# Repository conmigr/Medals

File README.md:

# Medals
PCB Medal Designs

Round shaped PCB designs using Eagle software that can be used as badges or awards.  These are a series of medals that can be used to help people learn the basics of making a PCB badge or iot device.

Nobel Prize Award - This PCB schematic and board usually is awarded to individuals for writing articles, blogs, or other material that contributess to the profession of information and cyber security.

Automator Award - This PCB schematic and board usually is awarded to individuals for outstanding work in the field of automation of an infosec practice.

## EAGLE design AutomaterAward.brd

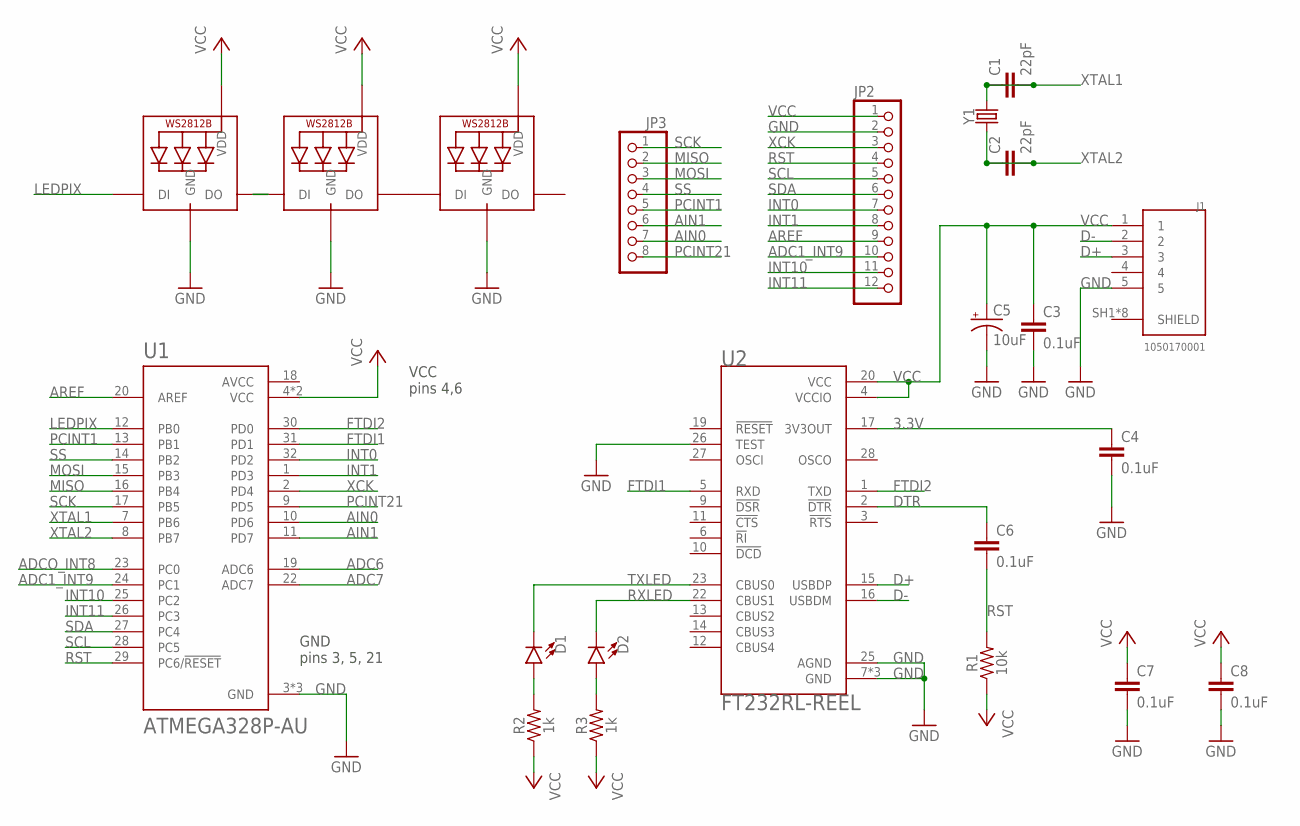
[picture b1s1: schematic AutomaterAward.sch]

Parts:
C1, C2: 22pF; 0603
C3, C4, C6, C7, C8: 0.1uF; 0603
C5: 10uF; EIA3216
D1, D2: LED0603; LED-0603
J1: 1050170001; MOLEX_1050170001
JP2: PINHD-1X12; 1X12
JP3: PINHD-1X8; 1X08
LED1, LED2, LED3: WS2812B3535; LED3535
R1: 10k; 0603
R2, R3: 1k; 0603
U1: ATMEGA328P-AU; QFP80P900X900X120-32N
U2: FT232RL-REEL; SOP65P780X200-28N
Y1: CRYSTALPTH-HC49US; HC49US

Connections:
3.3V: C4.1, U2.17 (3V3OUT)
ADC1_INT9: JP2.10, U1.24 (PC1)
ADC6: U1.19 (ADC6)
ADC7: U1.22 (ADC7)
ADCO_INT8: U1.23 (PC0)
AIN0: JP3.7, U1.10 (PD6)
AIN1: JP3.6, U1.11 (PD7)
AREF: JP2.9, U1.20 (AREF)
AVCC: U1.18 (AVCC)
D+: J1.3, U2.15 (USBDP)
D-: J1.2, U2.16 (USBDM)
DTR: C6.1, U2.2 (!DTR)
FTDI1: U1.31 (PD1), U2.5 (RXD)
FTDI2: U1.30 (PD0), U2.1 (TXD)
GND: C3.2, C4.2, C5.-, C7.2, C8.2, J1.5, JP2.2, LED1.4 (GND), LED2.4 (GND), LED3.4 (GND), U1.3 (GND), U1.5 (GND), U1.21 (GND), U2.7 (GND), U2.18 (GND), U2.21 (GND), U2.25 (AGND), U2.26 (TEST)
INT0: JP2.7, U1.32 (PD2)
INT1: JP2.8, U1.1 (PD3)
INT10: JP2.11, U1.25 (PC2)
INT11: JP2.12, U1.26 (PC3)
LEDPIX: LED1.1 (DI), U1.12 (PB0)
MISO: JP3.2, U1.16 (PB4)
MOSI: JP3.3, U1.15 (PB3)
unnamed: LED1.3 (DO), LED2.1 (DI)
unnamed: D1.A, R2.2
unnamed: D2.A, R3.2
unnamed: LED2.3 (DO), LED3.1 (DI)
PCINT1: JP3.5, U1.13 (PB1)
PCINT21: JP3.8, U1.9 (PD5)
RST: C6.2, JP2.4, R1.2, U1.29 (PC6/!RESET)
RXLED: D2.C, U2.22 (CBUS1)
SCK: JP3.1, U1.17 (PB5)
SCL: JP2.5, U1.28 (PC5)
SDA: JP2.6, U1.27 (PC4)
SS: JP3.4, U1.14 (PB2)
TXLED: D1.C, U2.23 (CBUS0)
VCC: C3.1, C5.+, C7.1, C8.1, J1.1, JP2.1, LED1.2 (VDD), LED2.2 (VDD), LED3.2 (VDD), R1.1, R2.1, R3.1, U1.4 (VCC), U1.6 (VCC), U2.4 (VCCIO), U2.20 (VCC)
XCK: JP2.3, U1.2 (PD4)
XTAL1: C1.1, C1.2, U1.7 (PB6), Y1.2
XTAL2: C2.1, C2.2, U1.8 (PB7), Y1.1

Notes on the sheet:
GND pins 3, 5, 21
VCC pins 4,6

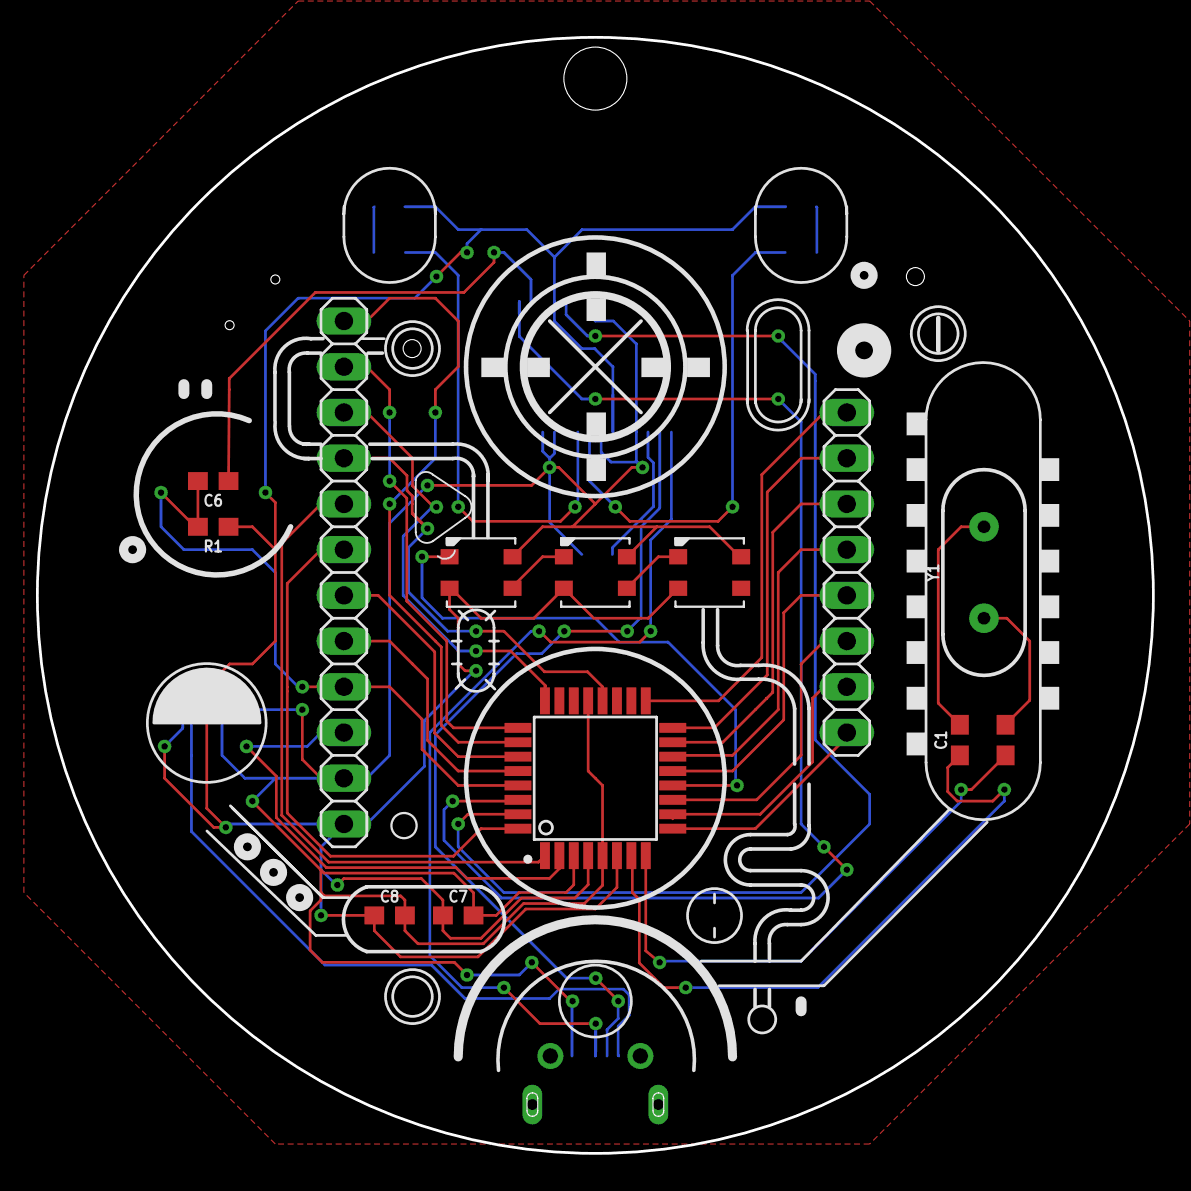
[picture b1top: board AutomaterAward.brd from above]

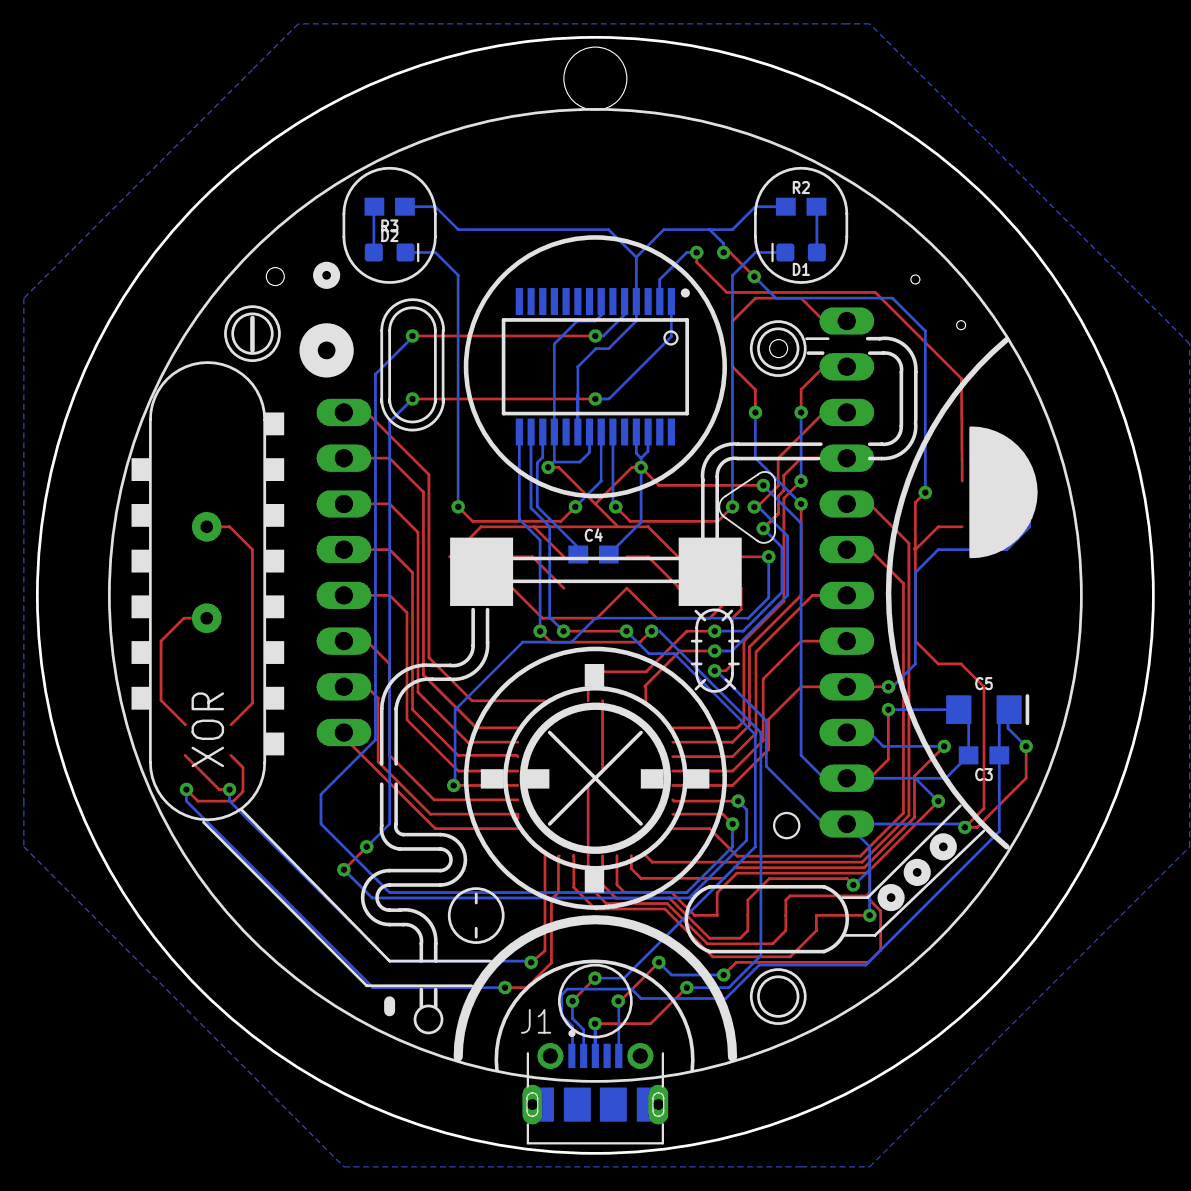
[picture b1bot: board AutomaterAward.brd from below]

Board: 2 copper layers, 62.0 x 62.0 mm, 22 parts (9 on the bottom side), 35 nets.

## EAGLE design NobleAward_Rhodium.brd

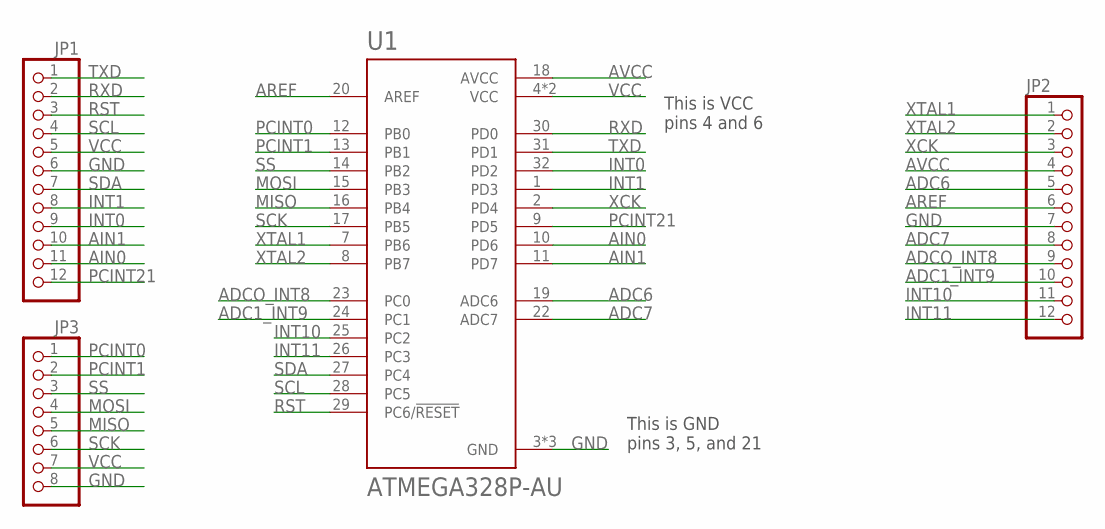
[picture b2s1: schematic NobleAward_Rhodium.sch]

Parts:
JP1, JP2: PINHD-1X12; 1X12
JP3: PINHD-1X8; 1X08
U1: ATMEGA328P-AU; QFP80P900X900X120-32N

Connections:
ADC1_INT9: JP2.10, U1.24 (PC1)
ADC6: JP2.5, U1.19 (ADC6)
ADC7: JP2.8, U1.22 (ADC7)
ADCO_INT8: JP2.9, U1.23 (PC0)
AIN0: JP1.11, U1.10 (PD6)
AIN1: JP1.10, U1.11 (PD7)
AREF: JP2.6, U1.20 (AREF)
AVCC: JP2.4, U1.18 (AVCC)
GND: JP1.6, JP2.7, JP3.8, U1.3 (GND), U1.5 (GND), U1.21 (GND)
INT0: JP1.9, U1.32 (PD2)
INT1: JP1.8, U1.1 (PD3)
INT10: JP2.11, U1.25 (PC2)
INT11: JP2.12, U1.26 (PC3)
MISO: JP3.5, U1.16 (PB4)
MOSI: JP3.4, U1.15 (PB3)
PCINT0: JP3.1, U1.12 (PB0)
PCINT1: JP3.2, U1.13 (PB1)
PCINT21: JP1.12, U1.9 (PD5)
RST: JP1.3, U1.29 (PC6/!RESET)
RXD: JP1.2, U1.30 (PD0)
SCK: JP3.6, U1.17 (PB5)
SCL: JP1.4, U1.28 (PC5)
SDA: JP1.7, U1.27 (PC4)
SS: JP3.3, U1.14 (PB2)
TXD: JP1.1, U1.31 (PD1)
VCC: JP1.5, JP3.7, U1.4 (VCC), U1.6 (VCC)
XCK: JP2.3, U1.2 (PD4)
XTAL1: JP2.1, U1.7 (PB6)
XTAL2: JP2.2, U1.8 (PB7)

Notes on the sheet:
This is GND pins 3, 5, and 21
This is VCC pins 4 and 6

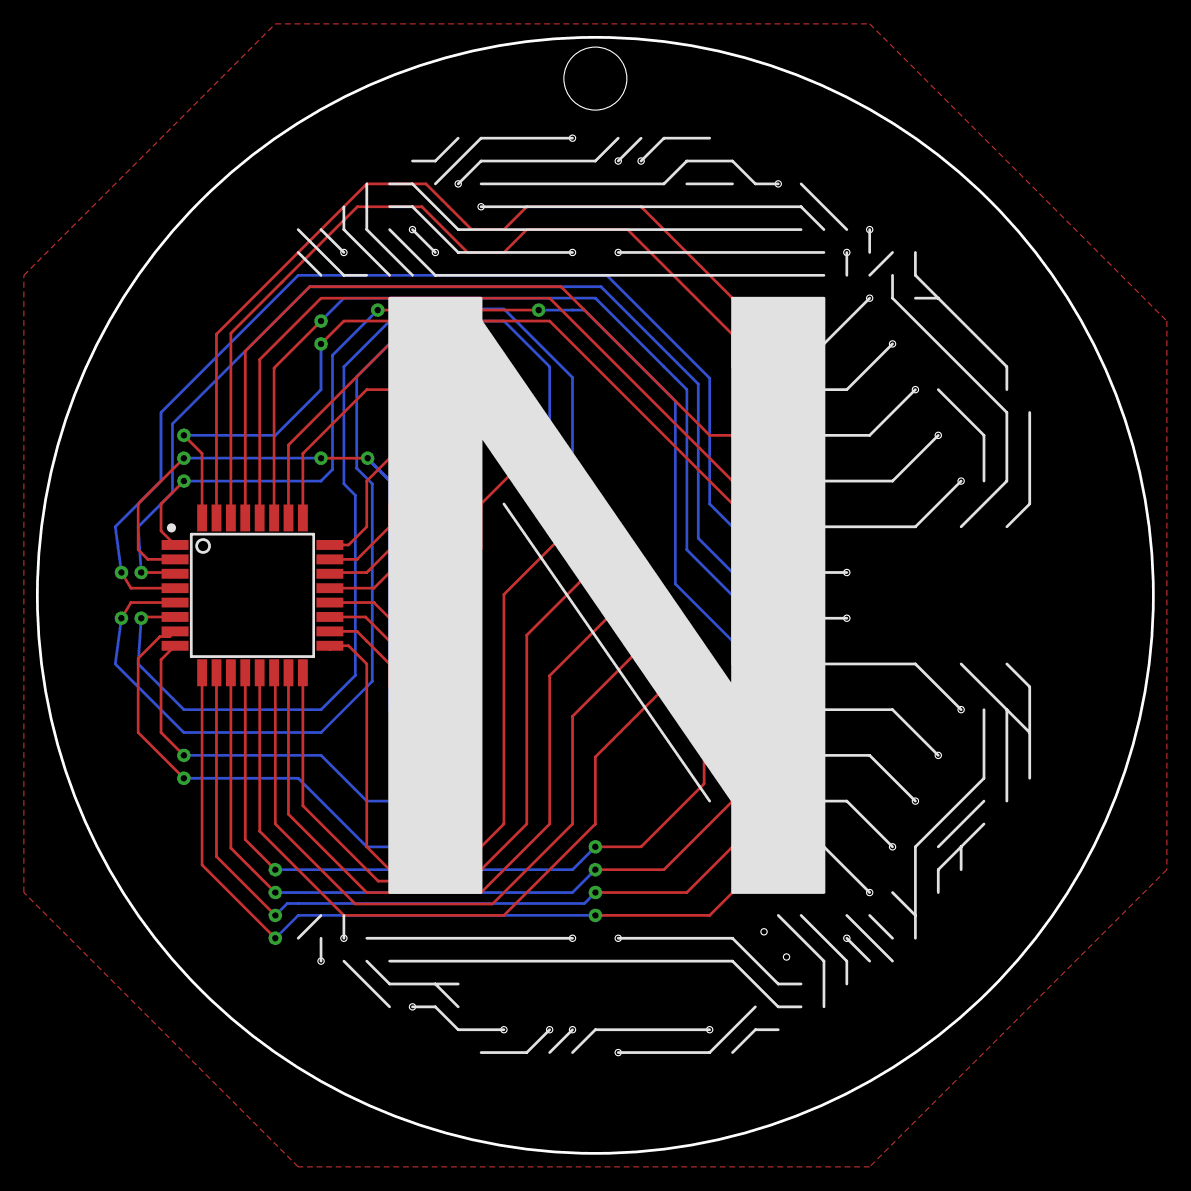
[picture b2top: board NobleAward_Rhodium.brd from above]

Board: 2 copper layers, 62.0 x 62.0 mm, 4 parts (0 on the bottom side), 29 nets.

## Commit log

2021-08-31 Add files via upload
    Modified code message
2021-10-08 Add files via upload
    New medal design
2021-10-08 Update README.md
    Ppdates to award types and descriptions

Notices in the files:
parts and their libraries:
SparkFun-Clocks: Licensing: Creative Commons ShareAlike 4.0 International - https://creativecommons.org/licenses/by-sa/4.0
